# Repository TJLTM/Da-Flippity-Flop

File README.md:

# Da-Flippity-Flop
Was designed to take standard 5pin Extron serial cables 232/422 and convert themm to 485 without having to rewire devices. No real world use.

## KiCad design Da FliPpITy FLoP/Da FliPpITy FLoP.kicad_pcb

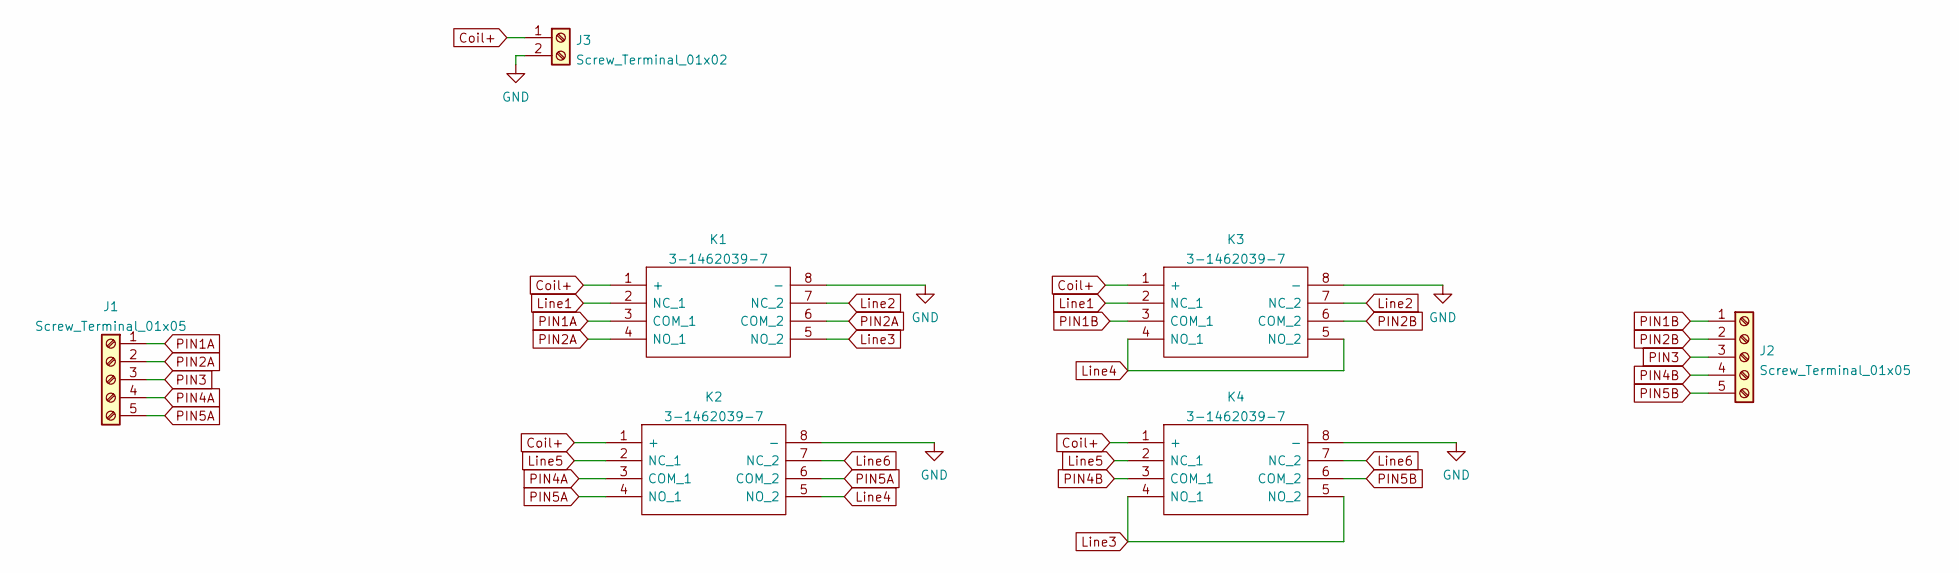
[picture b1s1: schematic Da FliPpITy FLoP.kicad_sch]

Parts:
J1, J2: Screw_Terminal_01x05; TerminalBlock_bornier-5_P5.08mm
J3: Screw_Terminal_01x02; TerminalBlock_bornier-2_P5.08mm
K1, K2, K3, K4: 3-1462039-7; 314620397; Mouser Part Number 655-3-1462039-7

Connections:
Coil+: J3.1, K1.1 (+), K2.1 (+), K3.1 (+), K4.1 (+)
GND: J3.2, K1.8 (-), K2.8 (-), K3.8 (-), K4.8 (-)
Line1: K1.2 (NC_1), K3.2 (NC_1)
Line2: K1.7 (NC_2), K3.7 (NC_2)
Line3: K1.5 (NO_2), K4.4 (NO_1), K4.5 (NO_2)
Line4: K2.5 (NO_2), K3.4 (NO_1), K3.5 (NO_2)
Line5: K2.2 (NC_1), K4.2 (NC_1)
Line6: K2.7 (NC_2), K4.7 (NC_2)
PIN1A: J1.1, K1.3 (COM_1)
PIN1B: J2.1, K3.3 (COM_1)
PIN2A: J1.2, K1.4 (NO_1), K1.6 (COM_2)
PIN2B: J2.2, K3.6 (COM_2)
PIN3: J1.3, J2.3
PIN4A: J1.4, K2.3 (COM_1)
PIN4B: J2.4, K4.3 (COM_1)
PIN5A: J1.5, K2.4 (NO_1), K2.6 (COM_2)
PIN5B: J2.5, K4.6 (COM_2)

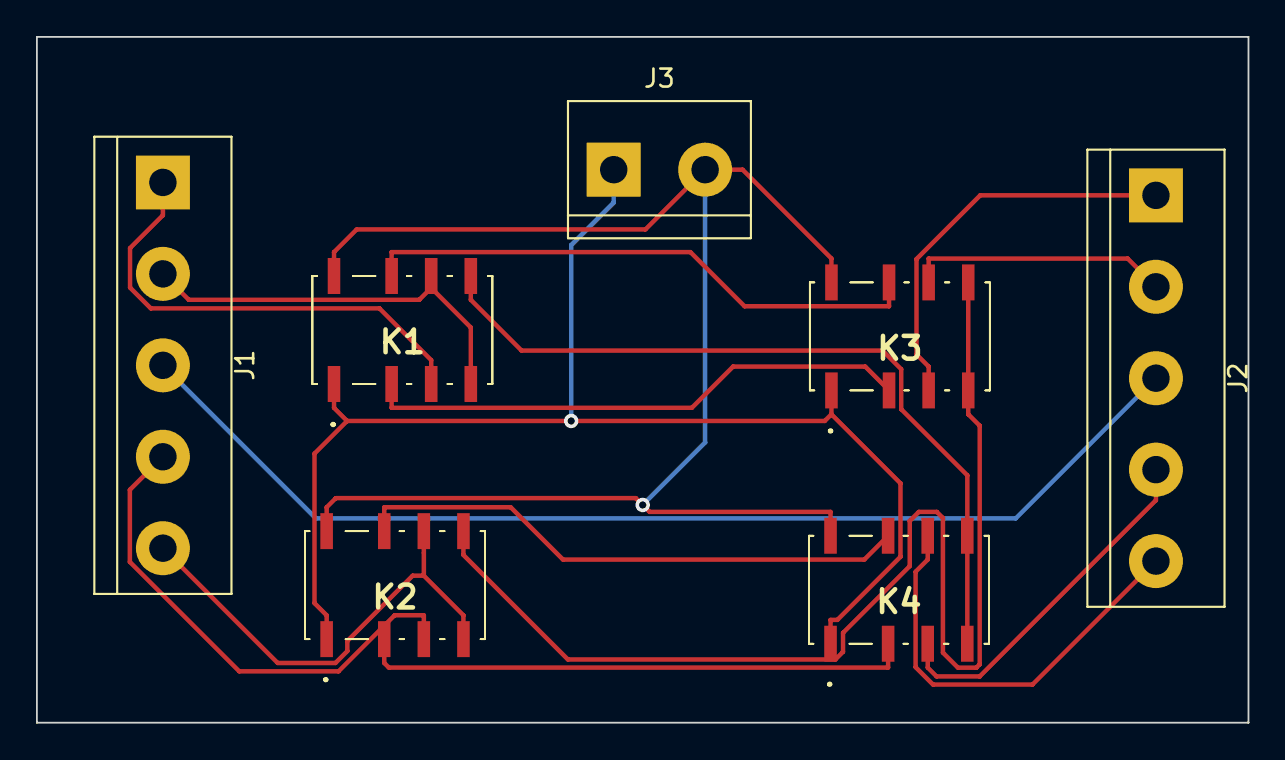
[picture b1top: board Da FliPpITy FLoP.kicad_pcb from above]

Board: 2 copper layers, 67.3 x 38.1 mm, 7 parts (0 on the bottom side), 17 nets.

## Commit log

2022-10-20 initial and probably last for this.
